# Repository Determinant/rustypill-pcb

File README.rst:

rustypill
---------

A uniform design for my daily/IoT DIY need.

Features
========

- STM32F103CBU6/STM32F411CEU6 microcontroller (required)
- All GPIOs are available
- Support optional HD44780 LCD (or "1602", with backlight) via I2C
- Support optional ESP8266 (WiFi module), via UART serial ports
- Support optional DS3231 (accurate RTC, with battery) via I2C
- Support optional AT24Cx (EEPROM) via I2C
- Support optional microSD via SPI
- Support optional custom I2C external board (such as OLED display)
- Convenient 10-pin IDC socket (A0-A7 which supports analog input, plus GND and V5 power)
- microUSB

PCB
===

.. image:: https://github.com/Determinant/rustypill/raw/master/pcb-top.png

.. image:: https://github.com/Determinant/rustypill/raw/master/pcb-bottom.png

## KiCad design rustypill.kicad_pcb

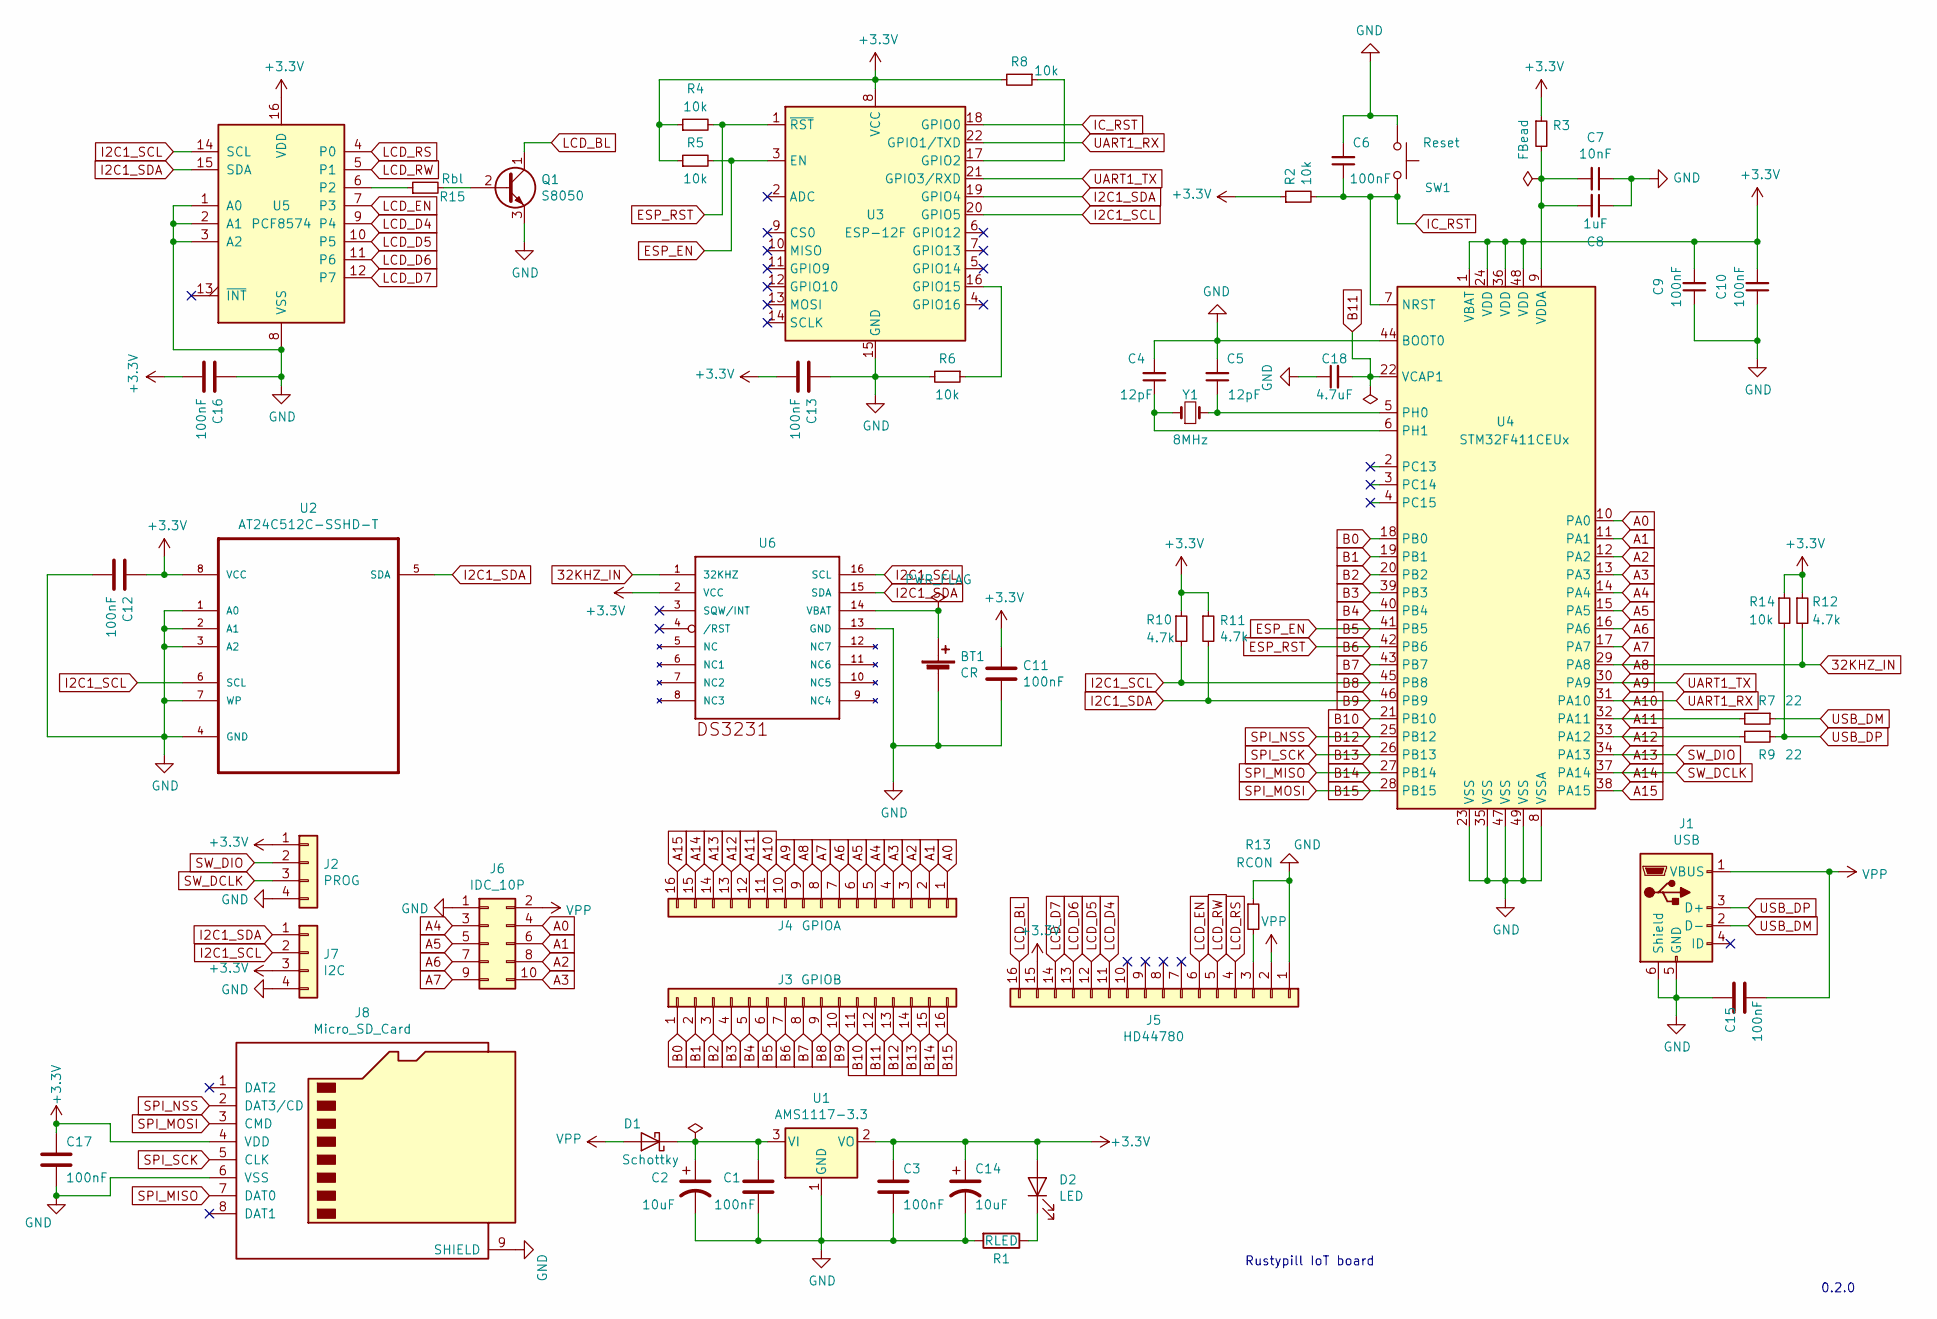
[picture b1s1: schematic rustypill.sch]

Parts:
BT1: CR; my3034_holder
C1, C3, C6, C9, C10, C11, C12, C13, C15, C16, C17: 100nF; C_0805_HandSoldering
C2, C14: 10uF; CP_Tantalum_Case-A_EIA-3216-18_Reflow
C4, C5: 12pF; C_0805_HandSoldering
C7: 10nF; C_0805_HandSoldering
C8: 1uF; C_0805_HandSoldering
C18: 4.7uF; C_0805_HandSoldering
D1: Schottky; D_0805
D2: LED; LED_0805_HandSoldering
J1: USB; USB_Micro-B_Molex-105017-0001
J2: PROG; PinHeader_1x04_P2.54mm_Horizontal
J3: GPIOB; PinHeader_1x16_P2.54mm_Vertical
J4: GPIOA; PinHeader_1x16_P2.54mm_Vertical
J5: HD44780; PinHeader_1x16_P2.54mm_Vertical
J6: IDC_10P; IDC-Header_2x05_P2.54mm_Vertical
J7: I2C; PinHeader_1x04_P2.54mm_Vertical
J8: Micro_SD_Card; 473340001
Q1: S8050; SOT-23
R1: RLED; R_0805_HandSoldering
R2, R4, R5, R6, R8, R14: 10k; R_0805_HandSoldering
R3: FBead; R_0805_HandSoldering
R7, R9: 22; R_0805_HandSoldering
R10, R11, R12: 4.7k; R_0805_HandSoldering
R13: RCON; R_0805_HandSoldering
R15: Rbl; R_0805_HandSoldering
SW1: Reset; SW_SPST_SKQG
U1: AMS1117-3.3; SOT-223-3_TabPin2
U2: AT24C512C-SSHD-T; SOIC127P600X175-8N
U3: ESP-12F; ESP-12E
U4: STM32F411CEUx; QFN50P700X700X60-49N-D
U5: PCF8574; VQFN-16-1EP_3x3mm_P0.5mm_EP1.68x1.68mm
U6: DS3231; SO16W
Y1: 8MHz; Crystal_SMD_5032-2pin_5.0x3.2mm_HandSoldering

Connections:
32KHZ_IN: J4.9, R12.2, U4.29 (PA8), U6.1 (32KHZ)
+3V3: C3.1, C9.2, C10.2, C11.1, C12.1, C13.2, C14.1, C16.2, C17.1, D2.2 (A), J2.1, J5.15, J7.3, J8.4 (VDD), R2.1, R3.1, R4.1, R5.1, R8.2, R10.1, R11.1, R12.1, R14.1, U1.2 (VO), U2.8 (VCC), U3.8 (VCC), U4.1 (VBAT), U4.24 (VDD), U4.36 (VDD), U4.48 (VDD), U5.16 (VDD), U6.2 (VCC); also elsewhere on the board
A0: J4.1, J6.4, U4.10 (PA0)
A1: J4.2, J6.6, U4.11 (PA1)
A2: J4.3, J6.8, U4.12 (PA2)
A3: J4.4, J6.10, U4.13 (PA3)
A4: J4.5, J6.3, U4.14 (PA4)
A5: J4.6, J6.5, U4.15 (PA5)
A6: J4.7, J6.7, U4.16 (PA6)
A7: J4.8, J6.9, U4.17 (PA7)
A9: J4.10, U3.21 (GPIO3/RXD), U4.30 (PA9)
A10: J4.11, U3.22 (GPIO1/TXD), U4.31 (PA10)
A11: J4.12, R7.2, U4.32 (PA11)
A12: J4.13, R9.2, U4.33 (PA12)
A13: J2.2, J4.14, U4.34 (PA13)
A14: J2.3, J4.15, U4.37 (PA14)
A15: J4.16, U4.38 (PA15)
B0: J3.1, U4.18 (PB0)
B1: J3.2, U4.19 (PB1)
B2: J3.3, U4.20 (PB2)
B3: J3.4, U4.39 (PB3)
B4: J3.5, U4.40 (PB4)
B5: J3.6, R5.2, U3.3 (EN), U4.41 (PB5)
B6: J3.7, R4.2, U3.1 (~RST), U4.42 (PB6)
B7: J3.8, U4.43 (PB7)
B8: J3.9, J7.2, R10.2, U2.6 (SCL), U3.20 (GPIO5), U4.45 (PB8), U5.14 (SCL), U6.16 (SCL)
B9: J3.10, J7.1, R11.2, U2.5 (SDA), U3.19 (GPIO4), U4.46 (PB9), U5.15 (SDA), U6.15 (SDA)
B10: J3.11, U4.21 (PB10)
B11: C18.2, J3.12, U4.22 (VCAP1)
B12: J3.13, J8.2 (DAT3/CD), U4.25 (PB12); also elsewhere on the board
B13: J3.14, J8.5 (CLK), U4.26 (PB13)
B14: J3.15, J8.7 (DAT0), U4.27 (PB14)
B15: J3.16, J8.3 (CMD), U4.28 (PB15)
ESP_BOOT0: C6.1, R2.2, SW1.2, U3.18 (GPIO0), U4.7 (NRST)
GND: BT1.2 (-), C1.2, C2.2, C3.2, C4.2, C5.2, C6.2, C7.1, C8.1, C9.1, C10.1, C11.2, C12.2, C13.1, C14.2, C15.1, C16.1, C17.2, C18.1, J1.5 (GND), J1.6 (Shield), J2.4, J5.1, J6.1, J7.4, J8.6 (VSS), J8.9 (SHIELD), Q1.3 (E), R1.2, R6.2, R13.1, SW1.1, U1.1 (GND), U2.1 (A0), U2.2 (A1), U2.3 (A2), U2.4 (GND), U2.7 (WP), U3.15 (GND), U4.8 (VSSA), U4.23 (VSS), U4.35 (VSS), U4.44 (BOOT0), U4.47 (VSS), U4.49 (VSS), U5.1 (A0), U5.2 (A1), U5.3 (A2), U5.8 (VSS), U6.13 (GND)
LCD_BL: J5.16, Q1.1 (C)
LCD_D4: J5.11, U5.9 (P4)
LCD_D5: J5.12, U5.10 (P5)
LCD_D6: J5.13, U5.11 (P6)
LCD_D7: J5.14, U5.12 (P7)
LCD_EN: J5.6, U5.7 (P3)
LCD_RS: J5.4, U5.4 (P0)
LCD_RW: J5.5, U5.5 (P1)
unnamed: BT1.1 (+), U6.14 (VBAT)
unnamed: C1.1, C2.1, D1.1 (K), U1.3 (VI)
unnamed: C4.1, U4.6 (PH1), Y1.1
unnamed: C5.1, U4.5 (PH0), Y1.2
unnamed: C7.2, C8.2, R3.2, U4.9 (VDDA)
unnamed: D2.1 (K), R1.1
unnamed: J5.3, R13.2
unnamed: Q1.2 (B), R15.2
unnamed: R6.1, U3.16 (GPIO15)
unnamed: R8.1, U3.17 (GPIO2)
unnamed: R15.1, U5.6 (P2)
unnamed 62: U4.2 (PC13); also elsewhere on the board
USB_DM: J1.2 (D-), R7.1
USB_DP: J1.3 (D+), R9.1, R14.2
VPP: C15.2, D1.2 (A), J1.1 (VBUS), J5.2, J6.2

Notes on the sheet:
Rustypill IoT board
0.2.0

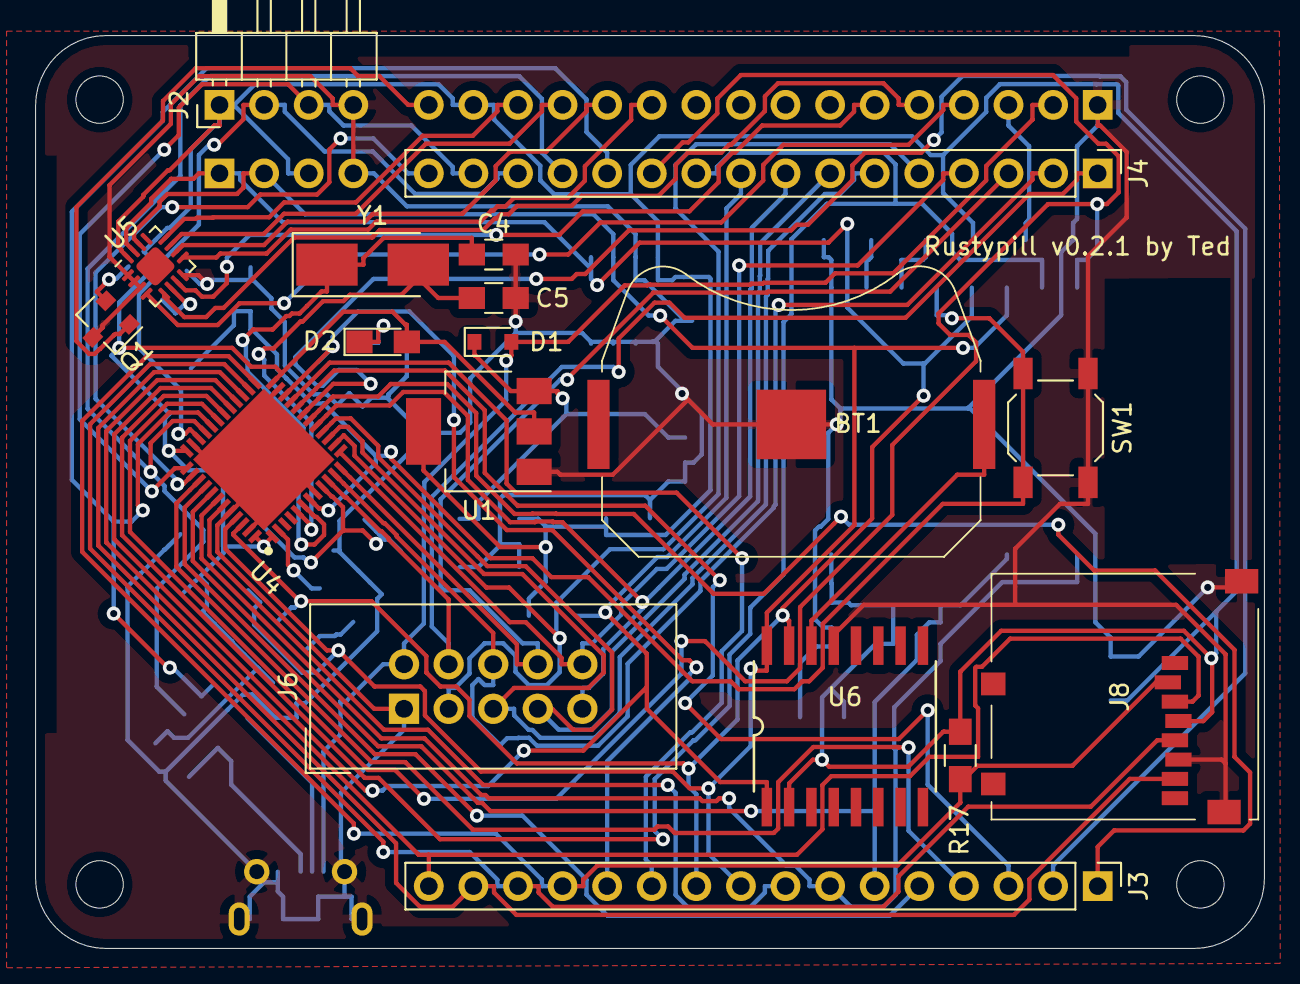
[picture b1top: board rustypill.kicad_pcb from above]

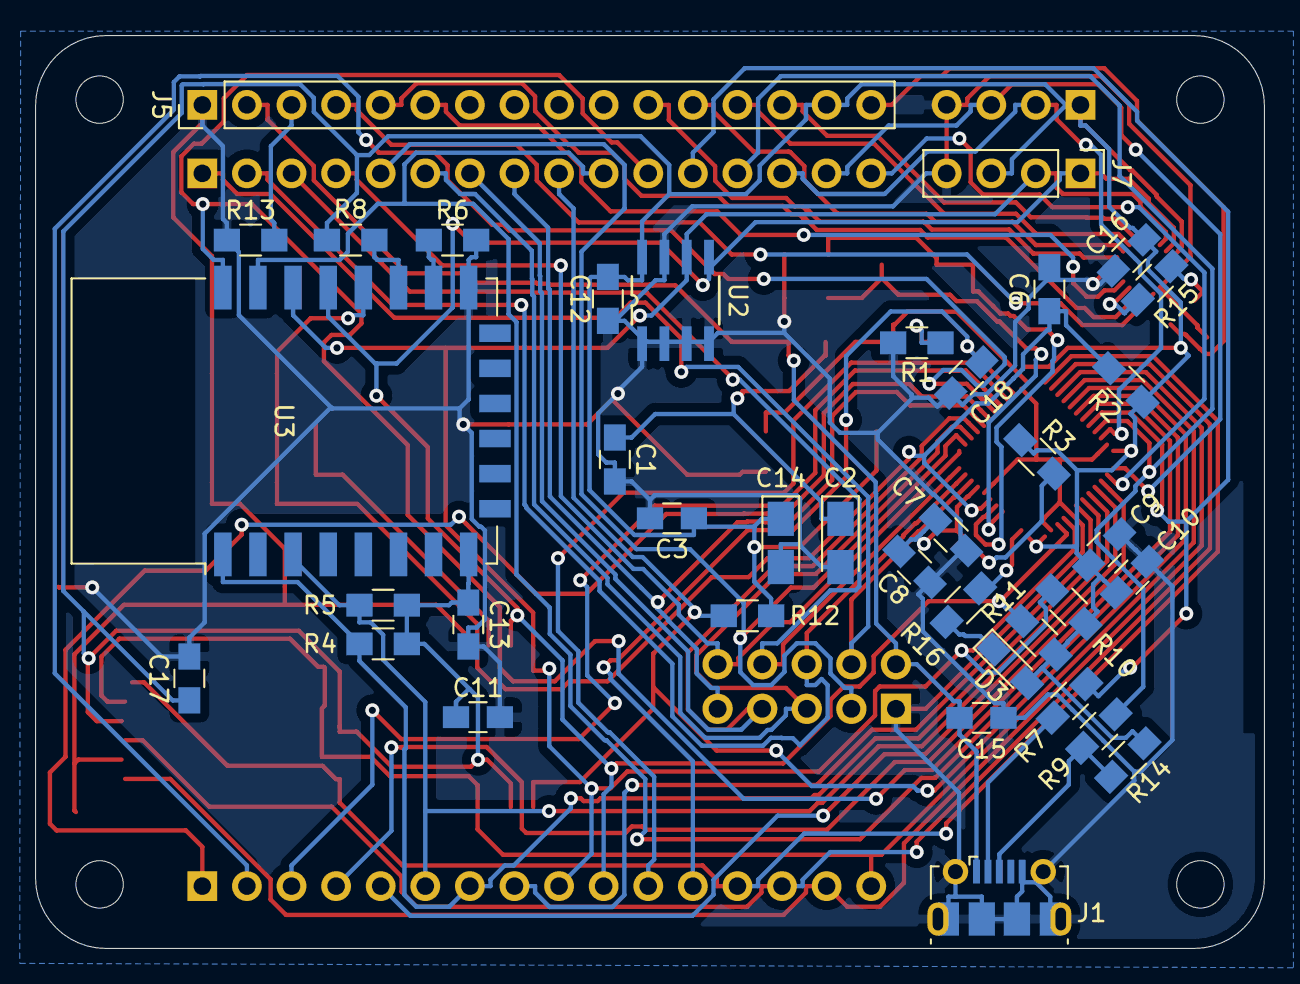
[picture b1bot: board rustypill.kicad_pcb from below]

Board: 2 copper layers, 70.0 x 52.0 mm, 60 parts (38 on the bottom side), 59 nets.

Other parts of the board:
 M1: MountingHole_2.7mm_M2.5
D3: LED; LED_0805_HandSoldering
M2, M3, M4: MountingHole_2.7mm_M2.5
R16: RLED; R_0805_HandSoldering
R17: 47k; R_0805_HandSoldering

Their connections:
+3V3: D3.2, R17.1; also elsewhere on the board
B12: R17.2; also elsewhere on the board
unnamed: D3.1, R16.2
unnamed 62: R16.1; also elsewhere on the board

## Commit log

2019-11-05 init
2019-11-07 finish pcb design
2019-11-07 finish v0.1.0
2019-11-07 add readme
2019-11-07 typo
2019-11-07 remove copper near the antenna
2019-11-10 add more I2C features; better placement; etc
2019-11-10 v0.2.0
2019-11-10 reduce vias
2019-11-12 finish routing
2019-12-11 clean up
2019-12-16 finish v0.2.0
2020-01-11 fix the sdcard orientation issue
